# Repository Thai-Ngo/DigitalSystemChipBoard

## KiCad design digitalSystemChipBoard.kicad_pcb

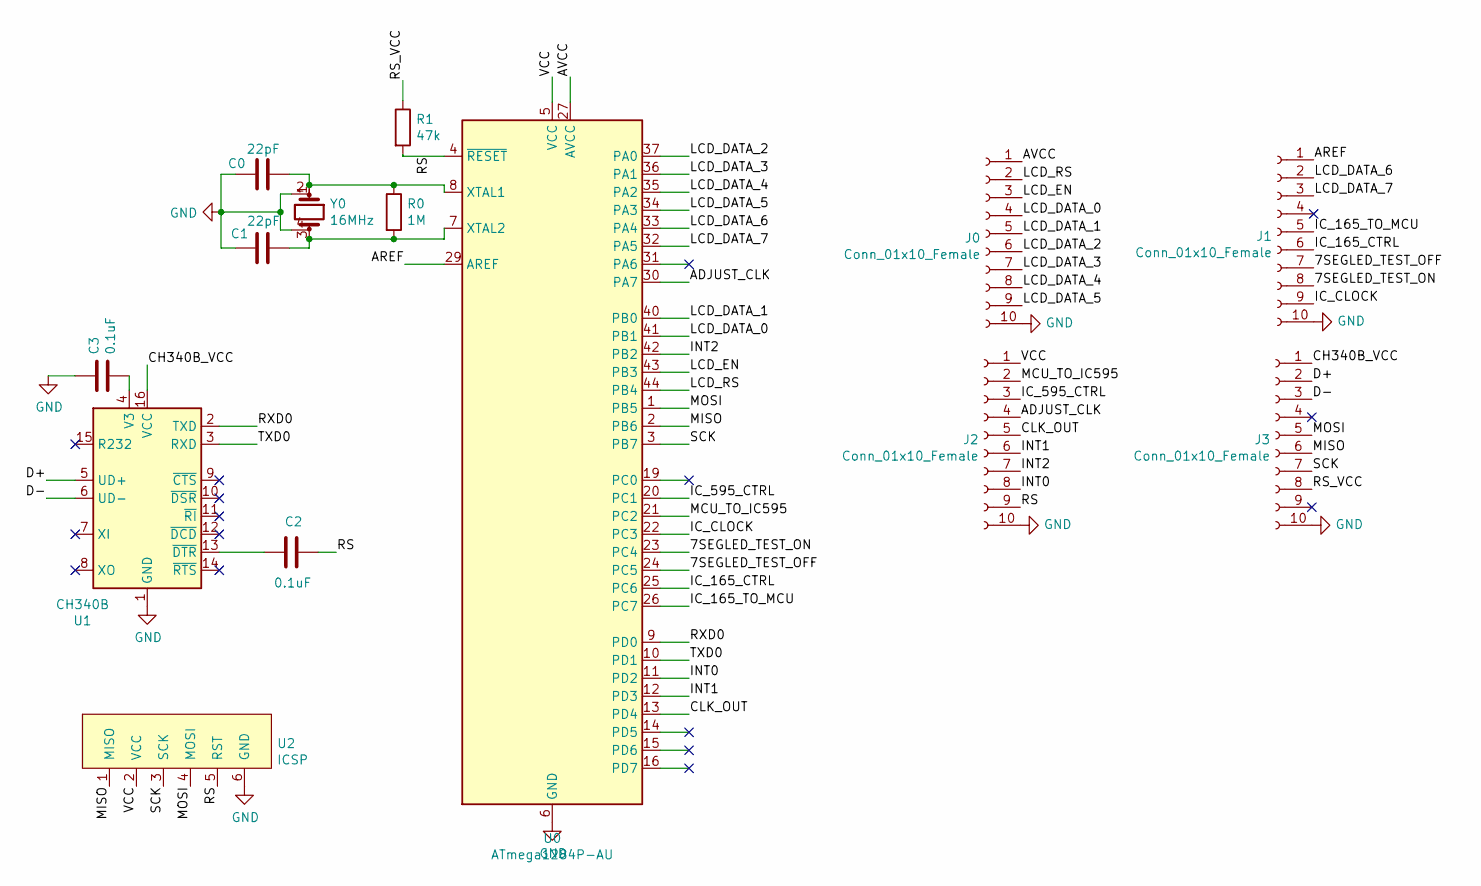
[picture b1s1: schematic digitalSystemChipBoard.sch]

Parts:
C0, C1: 22pF; C_0603_1608Metric; LCSC C105620
C2, C3: 0.1uF; C_0603_1608Metric; LCSC C14663
J0, J1, J2, J3: Conn_01x10_Female; PinHeader_1x10_P2.00mm_Vertical
R0: 1M; R_0603_1608Metric; LCSC C26098
R1: 47k; R_0603_1608Metric; LCSC C25819
U0: ATmega1284P-AU; TQFP-44_10x10mm_P0.8mm; LCSC C33575
U1: CH340B; SOIC-16_3.9x9.9mm_P1.27mm; LCSC C81010
U2: ICSP; ICSP_no_solder
Y0: 16MHz; Crystal_SMD_Abracon_ABM3B-4Pin_5.0x3.2mm; LCSC C258963

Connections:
/7SEGLED_TEST_OFF: J1.7, U0.24 (PC5)
/7SEGLED_TEST_ON: J1.8, U0.23 (PC4)
/ADJUST_CLK: J2.4, U0.30 (PA7)
/AREF: J1.1, U0.29 (AREF)
/AVCC: J0.1, U0.27 (AVCC)
/CH340B_VCC: J3.1, U1.16 (VCC)
/CLK_OUT: J2.5, U0.13 (PD4)
/D+: J3.2, U1.5 (UD+)
/D-: J3.3, U1.6 (UD-)
/IC_165_CTRL: J1.6, U0.25 (PC6)
/IC_165_TO_MCU: J1.5, U0.26 (PC7)
/IC_595_CTRL: J2.3, U0.20 (PC1)
/IC_CLOCK: J1.9, U0.22 (PC3)
/INT0: J2.8, U0.11 (PD2)
/INT1: J2.6, U0.12 (PD3)
/INT2: J2.7, U0.42 (PB2)
/LCD_DATA_0: J0.4, U0.41 (PB1)
/LCD_DATA_1: J0.5, U0.40 (PB0)
/LCD_DATA_2: J0.6, U0.37 (PA0)
/LCD_DATA_3: J0.7, U0.36 (PA1)
/LCD_DATA_4: J0.8, U0.35 (PA2)
/LCD_DATA_5: J0.9, U0.34 (PA3)
/LCD_DATA_6: J1.2, U0.33 (PA4)
/LCD_DATA_7: J1.3, U0.32 (PA5)
/LCD_EN: J0.3, U0.43 (PB3)
/LCD_RS: J0.2, U0.44 (PB4)
/MCU_TO_IC595: J2.2, U0.21 (PC2)
/MISO: J3.6, U0.2 (PB6), U2.1 (MISO)
/MOSI: J3.5, U0.1 (PB5), U2.4 (MOSI)
/RS: C2.1, J2.9, R1.2, U0.4 (~RESET), U2.5 (RST)
/RS_VCC: J3.8, R1.1
/RXD0: U0.9 (PD0), U1.2 (TXD)
/SCK: J3.7, U0.3 (PB7), U2.3 (SCK)
/TXD0: U0.10 (PD1), U1.3 (RXD)
/VCC: J2.1, U0.5 (VCC), U0.17 (VCC), U0.38 (VCC), U2.2 (VCC)
GND: C0.1, C1.2, C3.1, J0.10, J1.10, J2.10, J3.10, U0.6 (GND), U0.18 (GND), U0.28 (GND), U0.39 (GND), U1.1 (GND), U2.6 (GND), Y0.2 (GND), Y0.4 (GND)
unnamed: C0.2, R0.1, U0.8 (XTAL1), Y0.1
unnamed: C1.1, R0.2, U0.7 (XTAL2), Y0.3
unnamed: C2.2, U1.13 (~DTR)
unnamed: C3.2, U1.4 (V3)

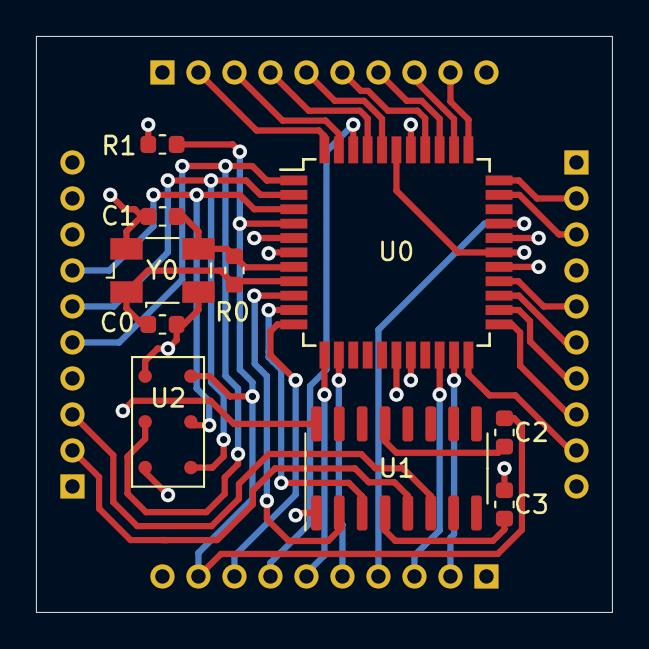
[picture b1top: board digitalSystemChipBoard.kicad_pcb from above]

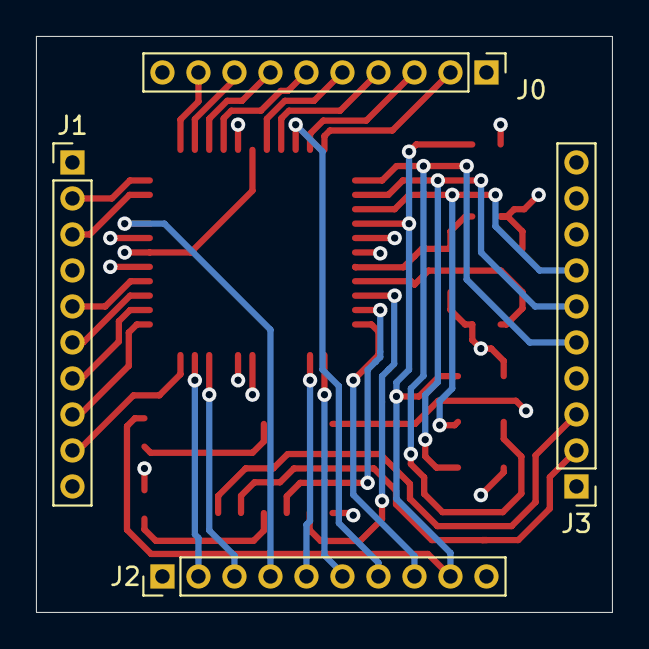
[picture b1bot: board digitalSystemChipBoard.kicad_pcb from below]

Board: 4 copper layers, 32.0 x 32.0 mm, 14 parts (4 on the bottom side), 40 nets.

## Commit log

2021-06-24 Fix small bug
2021-06-27 Edit some track
